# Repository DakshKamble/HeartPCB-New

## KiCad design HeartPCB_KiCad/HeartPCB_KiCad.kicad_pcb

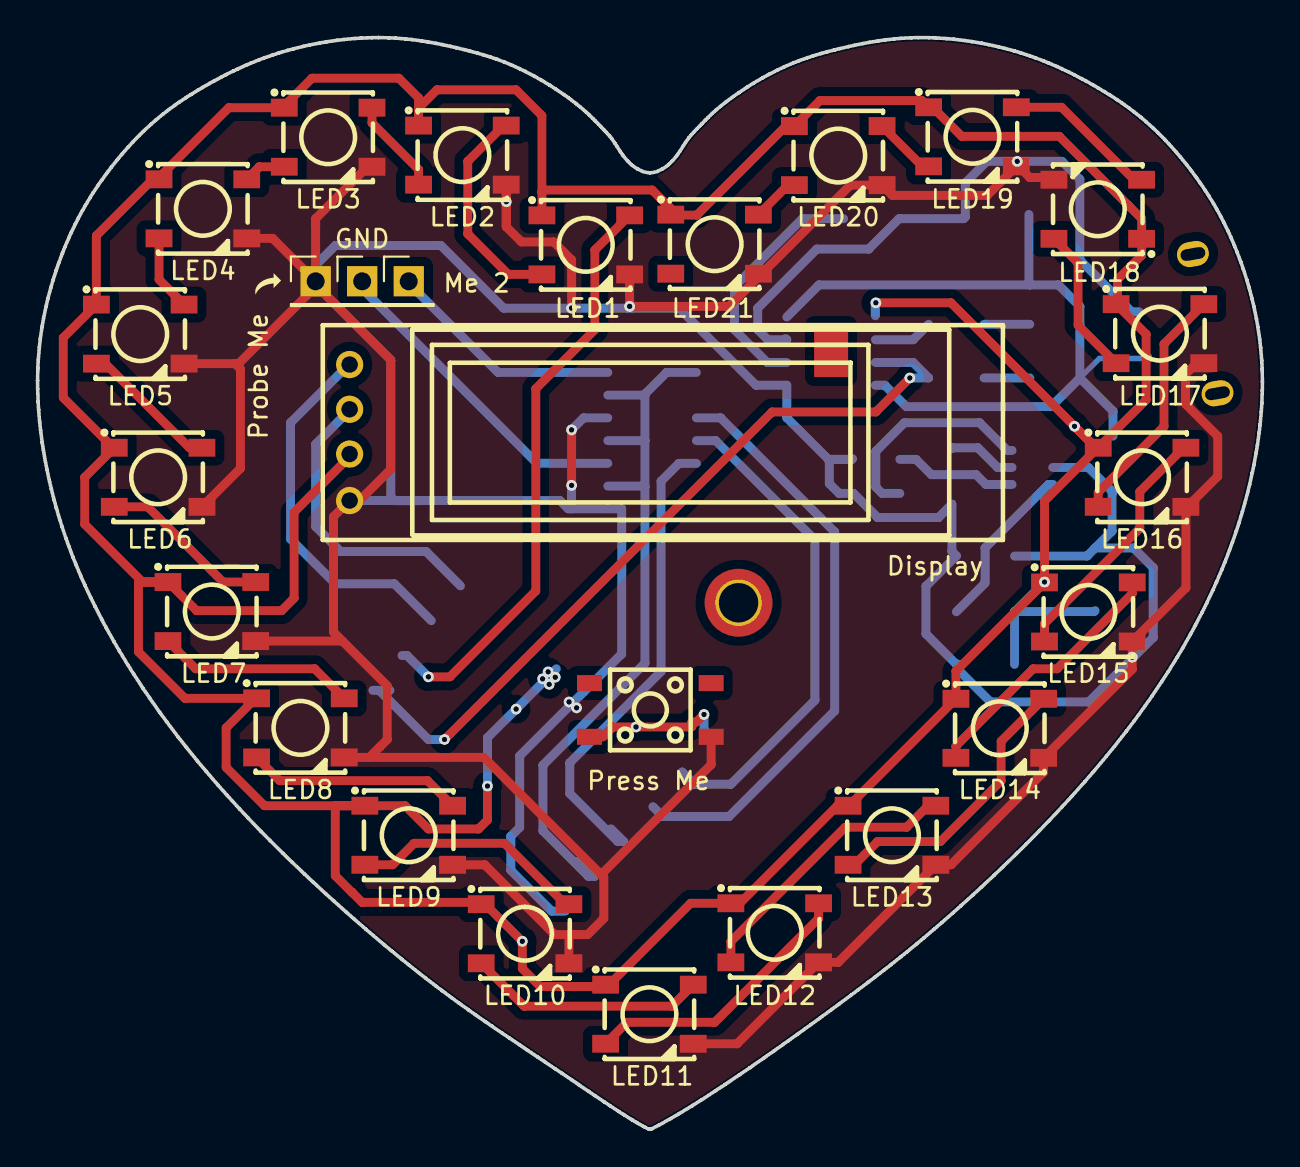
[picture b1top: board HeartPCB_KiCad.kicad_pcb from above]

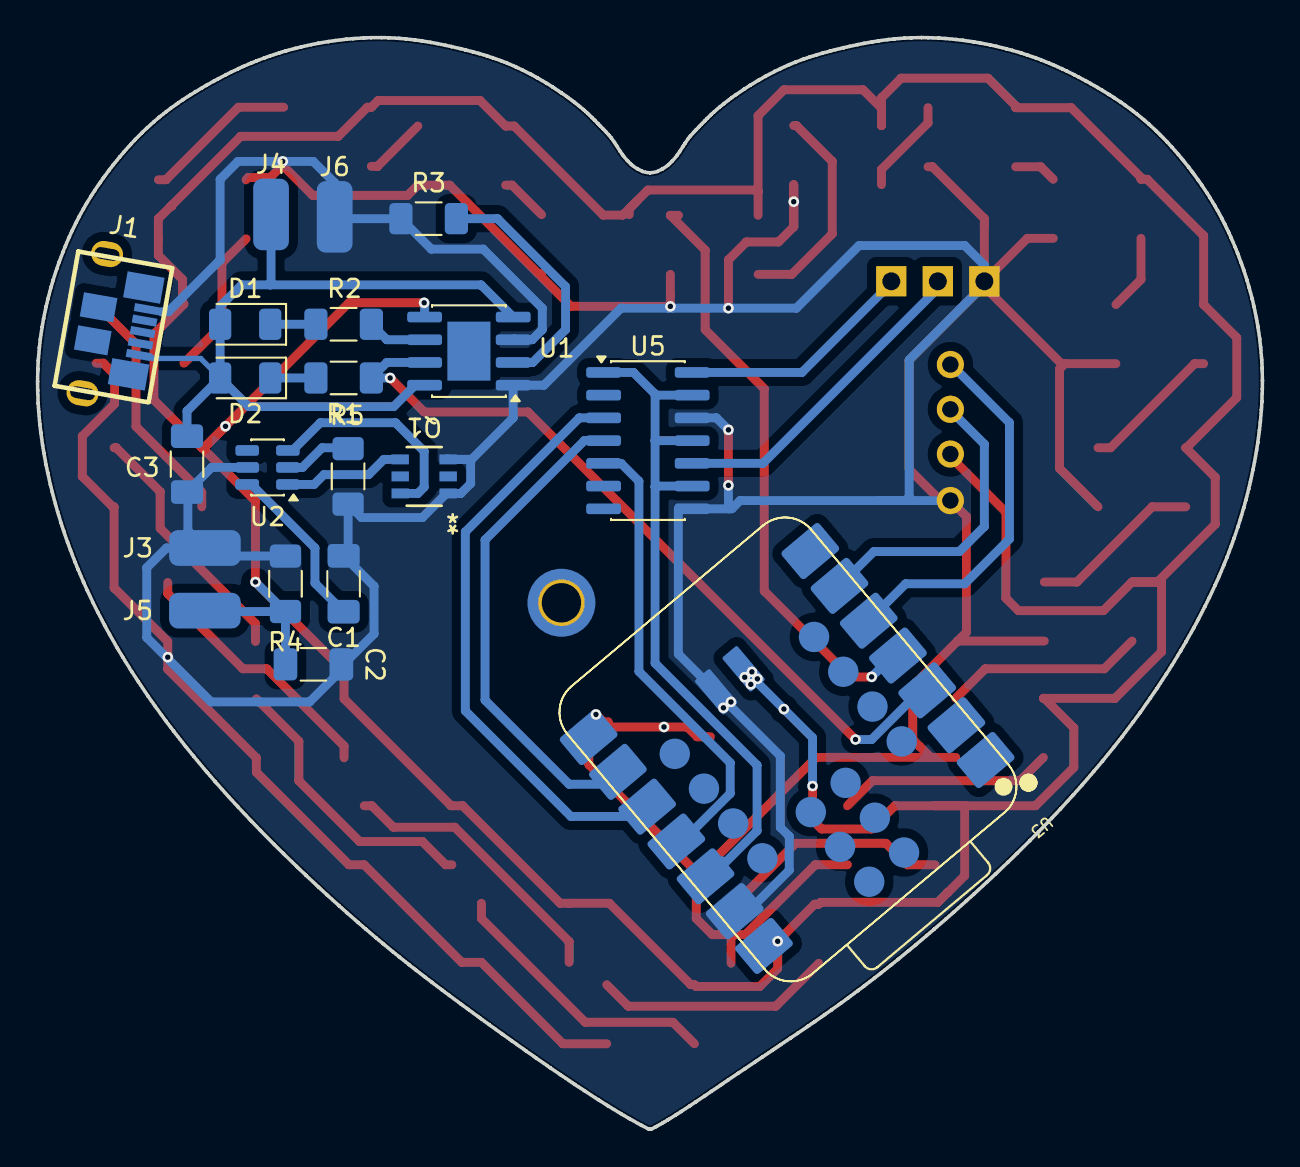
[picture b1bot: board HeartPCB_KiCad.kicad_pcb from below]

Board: 2 copper layers, 68.4 x 61.0 mm, 46 parts (20 on the bottom side), 42 nets.

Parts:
C1, C3: 100nF; C_1206_3216Metric_Pad1.33x1.80mm_HandSolder
C2: 10uF; C_1206_3216Metric_Pad1.33x1.80mm_HandSolder
D1: SDTBY; LED_1206_3216Metric
D2: CHRG; LED_1206_3216Metric
Display: 128x32-OLED-Module
GND: GND; PinHeader_1x01_P2.54mm_Vertical
J1: 1051640001; MICRO-USB-SMD_5P-P0.65-H-F_105164-0001
J3: IN-; SolderWirePad_1x01_SMD_2x4mm
J4: IN+; SolderWirePad_1x01_SMD_2x4mm
J5: B+; SolderWirePad_1x01_SMD_2x4mm
J6: B-; SolderWirePad_1x01_SMD_2x4mm
LED1, LED2, LED3, LED4, LED5, LED6, LED7, LED8, LED9, LED10, LED11, LED12, LED13, LED14, LED15, LED16, LED17, LED18, LED19, LED20, LED21: WS2812B; LED-SMD_4P-L5.0-W5.0-TL_WS2812B-B
Me 2: Probe Me; PinHeader_1x01_P2.54mm_Vertical
Press Me: SW_Push; SW-SMD_4P-L4.5-W4.5-P3.00-LS7.0
Probe Me: Me Too; PinHeader_1x01_P2.54mm_Vertical
Q1: FS8205A; SOT-23-6L_TCP
R1, R2, R5: 1k; R_1206_3216Metric_Pad1.30x1.75mm_HandSolder
R3: 1.2k; R_1206_3216Metric_Pad1.30x1.75mm_HandSolder
R4: 100; R_1206_3216Metric_Pad1.30x1.75mm_HandSolder
U1: TP4056-42-ESOP8; SOIC-8-1EP_3.9x4.9mm_P1.27mm_EP2.41x3.3mm_ThermalVias
U2: DW01A; SOT-23-6
U3: XIAO-RA4M1-SMD
U5: MCP4922; SOIC-14_3.9x8.7mm_P1.27mm

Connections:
+5V_USB: C3.1, D1.2 (A), D2.2 (A), J1.1 (VBUS), J4.1, U1.4 (V_{CC}), U1.8 (CE)
/CHRG: R1.2, U1.7 (~CHRG), U3.3 (D2)
/LED_Din: LED1.4 (DIN), U3.4 (D3)
/V_BAT: C2.2, Display.3 (VCC), J5.1, LED1.1 (VDD), LED2.1 (VDD), LED3.1 (VDD), LED4.1 (VDD), LED5.1 (VDD), LED6.1 (VDD), LED7.1 (VDD), LED8.1 (VDD), LED9.1 (VDD), LED10.1 (VDD), LED11.1 (VDD), LED12.1 (VDD), LED13.1 (VDD), LED14.1 (VDD), LED15.1 (VDD), LED16.1 (VDD), LED17.1 (VDD), LED18.1 (VDD), LED19.1 (VDD), LED20.1 (VDD), LED21.1 (VDD), R4.2, U1.5 (BAT), U3.14 (5V), U3.29 (BAT+)
GND: C1.2, C2.1, C3.2, Display.4 (GND), J1.5 (GND), J3.1, J6.1, LED1.3 (VSS), LED2.3 (VSS), LED3.3 (VSS), LED4.3 (VSS), LED5.3 (VSS), LED6.3 (VSS), LED7.3 (VSS), LED8.3 (VSS), LED9.3 (VSS), LED10.3 (VSS), LED11.3 (VSS), LED12.3 (VSS), LED13.3 (VSS), LED14.3 (VSS), LED15.3 (VSS), LED16.3 (VSS), LED17.3 (VSS), LED18.3 (VSS), LED19.3 (VSS), LED20.3 (VSS), LED21.3 (VSS), Press Me.1, Probe Me.1, Q1.1, Q1.3, R3.2, R4.1, R5.1, U1.1 (TEMP), U1.3 (GND), U2.5 (VCC), U3.13 (GND), U3.30 (BAT-), U5.8 (~LDAC), U5.12 (Vss)
unnamed: D1.1 (K), R2.1
unnamed: D2.1 (K), R1.1
unnamed: Me 2.1, U5.14 (VA)
unnamed: GND.1, U5.10 (VB)
unnamed: LED1.2 (DOUT), LED2.4 (DIN)
unnamed: LED2.2 (DOUT), LED3.4 (DIN)
unnamed: LED3.2 (DOUT), LED4.4 (DIN)
unnamed: LED4.2 (DOUT), LED5.4 (DIN)
unnamed: LED5.2 (DOUT), LED6.4 (DIN)
unnamed: LED6.2 (DOUT), LED7.4 (DIN)
unnamed: LED7.2 (DOUT), LED8.4 (DIN)
unnamed: LED8.2 (DOUT), LED9.4 (DIN)
unnamed: LED9.2 (DOUT), LED10.4 (DIN)
unnamed: LED10.2 (DOUT), LED11.4 (DIN)
unnamed: LED11.2 (DOUT), LED12.4 (DIN)
unnamed: LED12.2 (DOUT), LED13.4 (DIN)
unnamed: LED13.2 (DOUT), LED14.4 (DIN)
unnamed: LED14.2 (DOUT), LED15.4 (DIN)
unnamed: LED15.2 (DOUT), LED16.4 (DIN)
unnamed: LED16.2 (DOUT), LED17.4 (DIN)
unnamed: LED17.2 (DOUT), LED18.4 (DIN)
unnamed: LED18.2 (DOUT), LED19.4 (DIN)
unnamed: LED19.2 (DOUT), LED20.4 (DIN)
unnamed: LED20.2 (DOUT), LED21.4 (DIN)
unnamed: R3.1, U1.2 (PROG)
unnamed: R2.2, U1.6 (~STDBY)
unnamed: R5.2, U2.2 (CS)
unnamed: C1.1, U2.6 (GND)
unnamed: Q1.6, U2.3 (OC)
unnamed: Q1.4, U2.1 (OD)
unnamed: U3.12 (3V3), U5.1 (Vdd), U5.9 (~SHDN), U5.11 (VrefB), U5.13 (VrefA)
unnamed: Display.1 (SDA), U3.5 (D4)
unnamed: Display.2 (SCL), U3.6 (D5)
unnamed: Press Me.2, U3.8 (D7)
unnamed: U3.9 (D8), U5.4 (SCK)
unnamed: U3.10 (D9), U5.3 (~CS)
unnamed: U3.11 (D10), U5.5 (SDI)

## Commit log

2025-09-21 Working Menu system version 1
2025-09-21 working menu with local files v1
2025-09-21 added selection to menu items
2025-09-21 working propose mode menu function
2025-09-21 added splash screen
2025-10-03 working menu and simple animations
2025-10-03 working menu added battery features and animations
2025-10-08 ported for RA4M1
2025-10-08 added battery indication from led and changed ratio for new board
2025-10-17 added working oscillosope function using MCP4922 Dac ic
2025-10-17 added brightness control feature on longpress
2025-10-17 improved brightness menu
2025-10-19 Complete PCB in Kicad
2025-11-02 Added Ground Routing
2025-11-15 final version for order
2025-11-15 fixed ra4m1 footprint
2026-01-17 moved kicad files from old repo
2026-01-17 Added platformio project
2026-01-17 Ignore PlatformIO and VS Code generated files
